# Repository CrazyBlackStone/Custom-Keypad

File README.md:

# Custom-Keypad
This is a custom keypad originally made for osu.

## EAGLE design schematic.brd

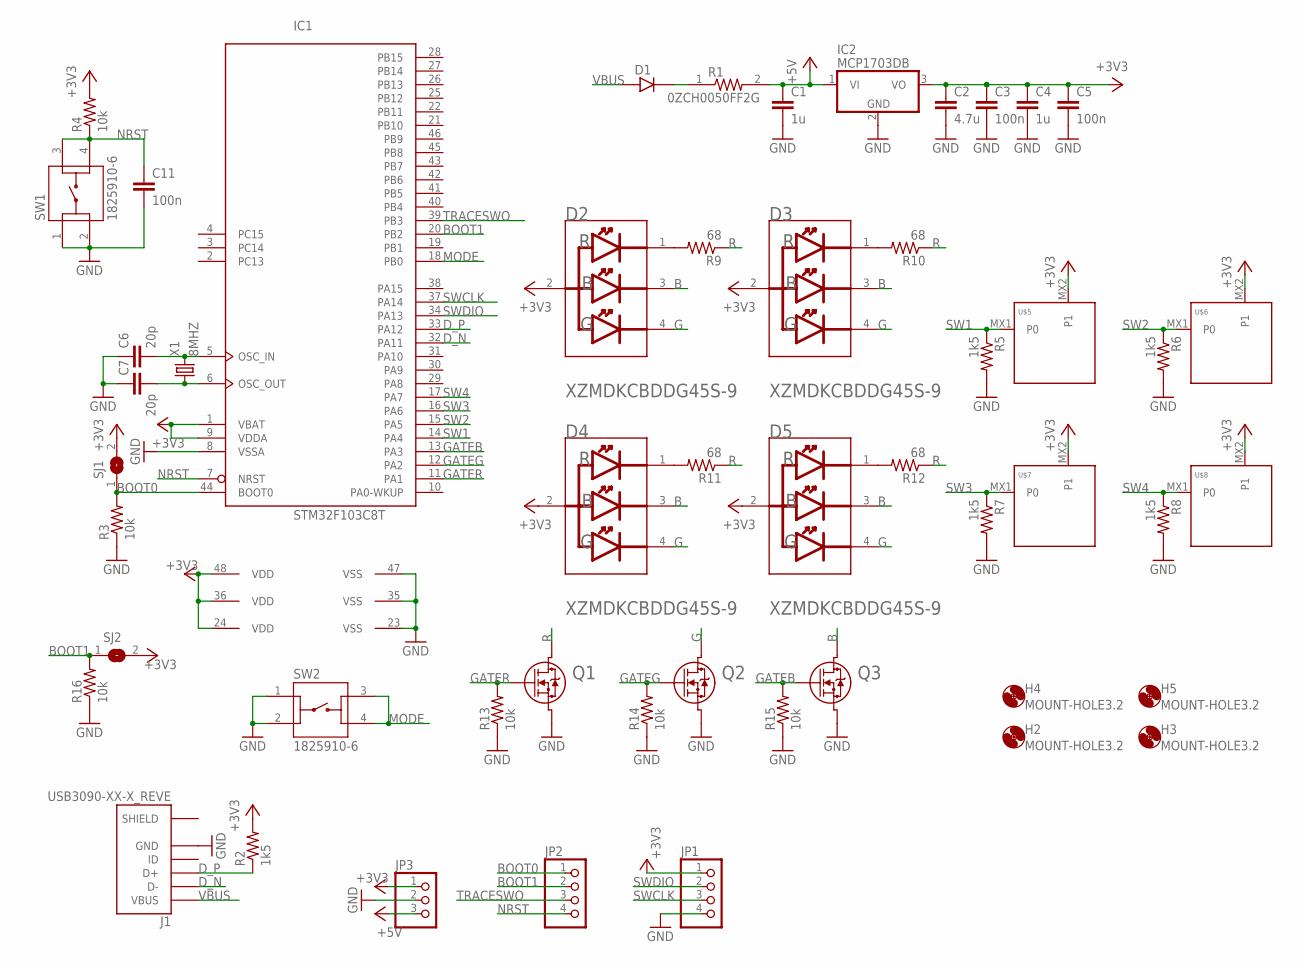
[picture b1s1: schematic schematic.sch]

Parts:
C1, C4: 1u; C0805
C2: 4.7u; C0805
C3, C5, C11: 100n; C0805
C6, C7: 20p; C0805
D1: DIODE_SOD123FL; SOD123FL
D2, D3, D4, D5: SUNLED_XZMDKCBDDG45S-9SUNLED_XZMDKCBDDG45S-9_0_0; SUNLED_XZMDKCBDDG45S-9_0
H2, H3, H4, H5: MOUNT-HOLE3.2; 3,2
IC1: STM32F103C8T; LQFP48
IC2: MCP1703DB; SOT223
J1: USB3090-XX-X_REVE; GCT_USB3090-XX-X_REVE
JP1, JP2: PINHD-1X4/90; 1X04/90
JP3: PINHD-1X3/90; 1X03/90
Q1, Q2, Q3: RK7002BMT116TRANS_RK7002BMHZG_ROM-M; TRANS_RK7002BMHZG_ROM-M
R1: 0ZCH0050FF2G; RESC3225X75N
R2, R5, R6, R7, R8: 1k5; R0805
R3, R4, R13, R14, R15, R16: 10k; R0805
R9, R10, R11, R12: 68; R0805
SJ1, SJ2: SJ
SW1, SW2: 1825910-6; SW_1825910-6-4
U$5, U$6, U$7, U$8: KEYSWITCH-PLAIN-MXHSPCB-1U; MXHSPCB-1U
X1: 8MHZ; HC49/S

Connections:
+3V3: C2.1, C3.1, C4.1, C5.1, D2.2 (COMMON_ANODE), D3.2 (COMMON_ANODE), D4.2 (COMMON_ANODE), D5.2 (COMMON_ANODE), IC1.1 (VBAT), IC1.9 (VDDA), IC1.24 (VDD), IC1.36 (VDD), IC1.48 (VDD), IC2.3 (VO), JP1.1, JP3.1, R2.2, R4.2, SJ1.2, SJ2.2, U$5.MX2 (P1), U$6.MX2 (P1), U$7.MX2 (P1), U$8.MX2 (P1)
+5V: C1.1, IC2.1 (VI), JP3.3, R1.2
B: D2.3 (BLUE_CATHODE), D3.3 (BLUE_CATHODE), D4.3 (BLUE_CATHODE), D5.3 (BLUE_CATHODE), Q3.3 (2)
BOOT0: IC1.44 (BOOT0), JP2.1, R3.2, SJ1.1
BOOT1: IC1.20 (PB2), JP2.2, R16.2, SJ2.1
D_N: IC1.32 (PA11), J1.2 (D-)
D_P: IC1.33 (PA12), J1.3 (D+), R2.1
G: D2.4 (GREEN_CATHODE), D3.4 (GREEN_CATHODE), D4.4 (GREEN_CATHODE), D5.4 (GREEN_CATHODE), Q2.3 (2)
GATEB: IC1.13 (PA3), Q3.1, R15.2
GATEG: IC1.12 (PA2), Q2.1, R14.2
GATER: IC1.11 (PA1), Q1.1, R13.2
GND: C1.2, C2.2, C3.2, C4.2, C5.2, C6.1, C7.1, C11.2, IC1.8 (VSSA), IC1.23 (VSS), IC1.35 (VSS), IC1.47 (VSS), IC2.2 (GND), J1.5 (GND), JP1.4, JP3.2, Q1.2 (3), Q2.2 (3), Q3.2 (3), R3.1, R5.2, R6.2, R7.2, R8.2, R13.1, R14.1, R15.1, R16.1, SW1.1, SW1.2, SW2.1, SW2.2
MODE: IC1.18 (PB0), SW2.3, SW2.4
unnamed: D2.1 (RED_CATHODE), R9.2
unnamed: D1.C, R1.1
unnamed: C6.2, IC1.5 (OSC_IN), X1.2
unnamed: C7.2, IC1.6 (OSC_OUT), X1.1
unnamed: D3.1 (RED_CATHODE), R10.2
unnamed: D4.1 (RED_CATHODE), R11.2
unnamed: D5.1 (RED_CATHODE), R12.2
NRST: C11.1, IC1.7 (NRST), JP2.4, R4.1, SW1.3, SW1.4
R: Q1.3 (2), R9.1, R10.1, R11.1, R12.1
SHIELD: J1.6 (SHIELD), J1.7 (SHIELD), J1.8 (SHIELD), J1.9 (SHIELD)
SW1: IC1.14 (PA4), R5.1, U$5.MX1 (P0)
SW2: IC1.15 (PA5), R6.1, U$6.MX1 (P0)
SW3: IC1.16 (PA6), R7.1, U$7.MX1 (P0)
SW4: IC1.17 (PA7), R8.1, U$8.MX1 (P0)
SWCLK: IC1.37 (PA14), JP1.3
SWDIO: IC1.34 (PA13), JP1.2
TRACESWO: IC1.39 (PB3), JP2.3
VBUS: D1.A, J1.1 (VBUS)

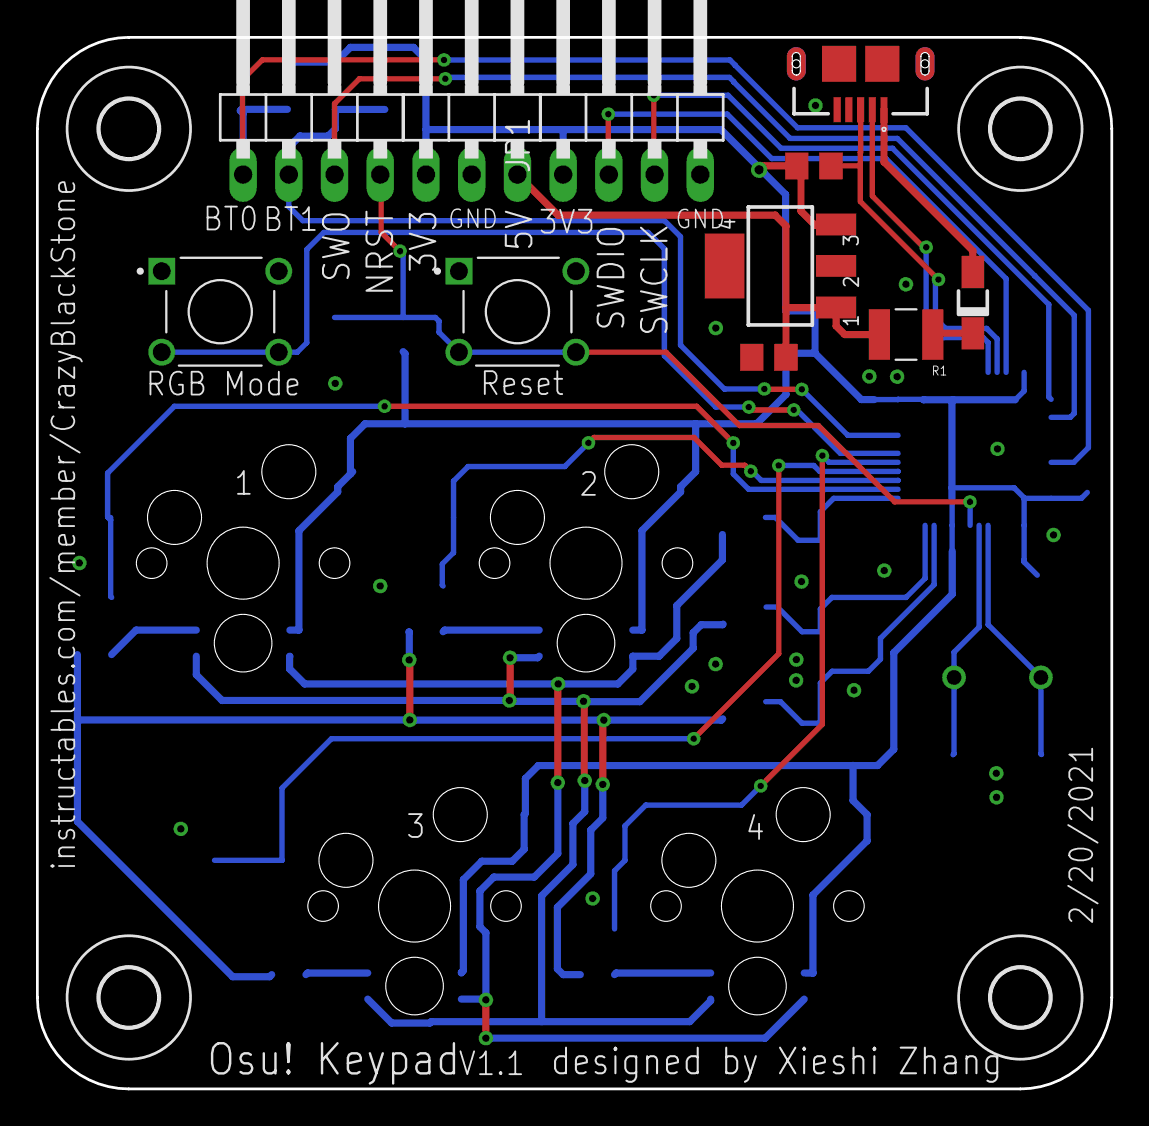
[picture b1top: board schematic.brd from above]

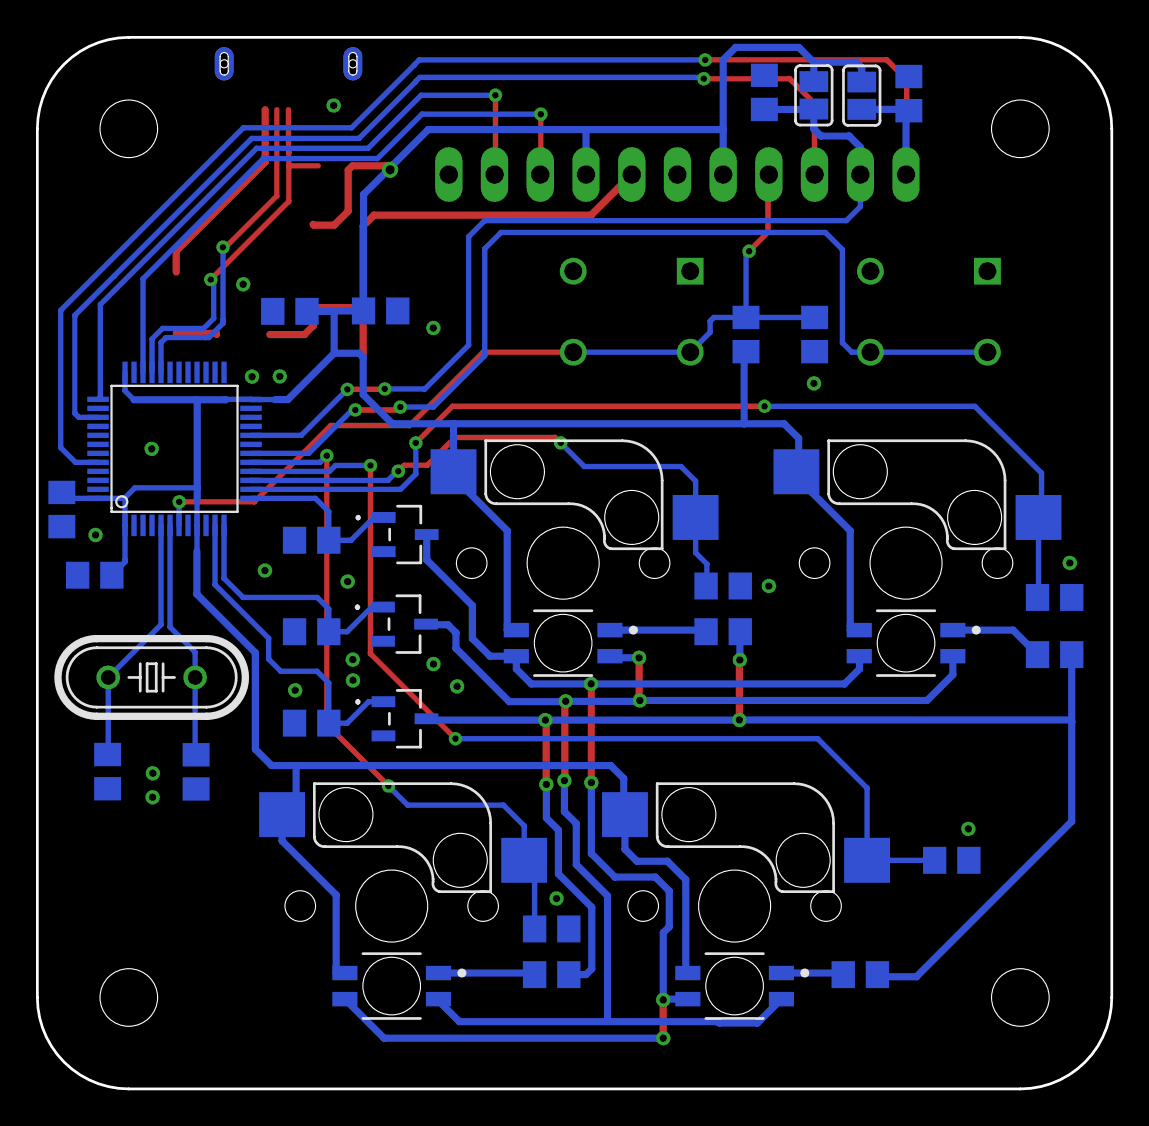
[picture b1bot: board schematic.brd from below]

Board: 2 copper layers, 59.7 x 58.4 mm, 51 parts (36 on the bottom side), 31 nets.

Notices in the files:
parts and their libraries:
COPYRIGHT: Copyright (C) 2018 Accelerated Designs. All rights reserved
